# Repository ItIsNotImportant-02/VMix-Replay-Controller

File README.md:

# vMix Replay Controller

Vlastní hardwarový ovladač pro vMix Replay ve stylu EVS: RGB tlačítka, páka pro rychlost, jog kolečko. Vlastní PCB (KiCad, osazení JLCPCB), vlastní firmware, 3D tištěná krabička.

- Plán projektu: [docs/PLAN.md](docs/PLAN.md)
- Dashboard postupu: https://claude.ai/artifact/F6eHfhQ5NSxDFNfWmzDA3g
- Deep Research prompty: [docs/research/](docs/research/)

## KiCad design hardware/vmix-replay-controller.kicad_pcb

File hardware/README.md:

# Hardware (KiCad 9)

Hlavní deska ovladače. Popis návrhu a otevřené body: [DESIGN.md](DESIGN.md), piny a mapování tlačítek/LED: [PINMAP.md](PINMAP.md).

- `vmix-replay-controller.kicad_pro` a `vmix-replay-controller.kicad_sch`: projekt a jednostránkové blokové schéma (generované z `tools/circuit.py` + `tools/layout.py`, needitovat ručně)
- `lib/`: vlastní symboly a footprinty (PB26, TS5, IS31FL3236A QFN-44)
- `tools/`: generátor schématu a footprintů (`gen.py`), kontrola netlistu (`verify.py`), rozmístění desky ze schématu (`pcb.py`) a export BOM + CPL pro JLCPCB (`jlc.py`)
- `production/`: výrobní data pro JLCPCB (Gerber, BOM, CPL), doplní se po návrhu desky

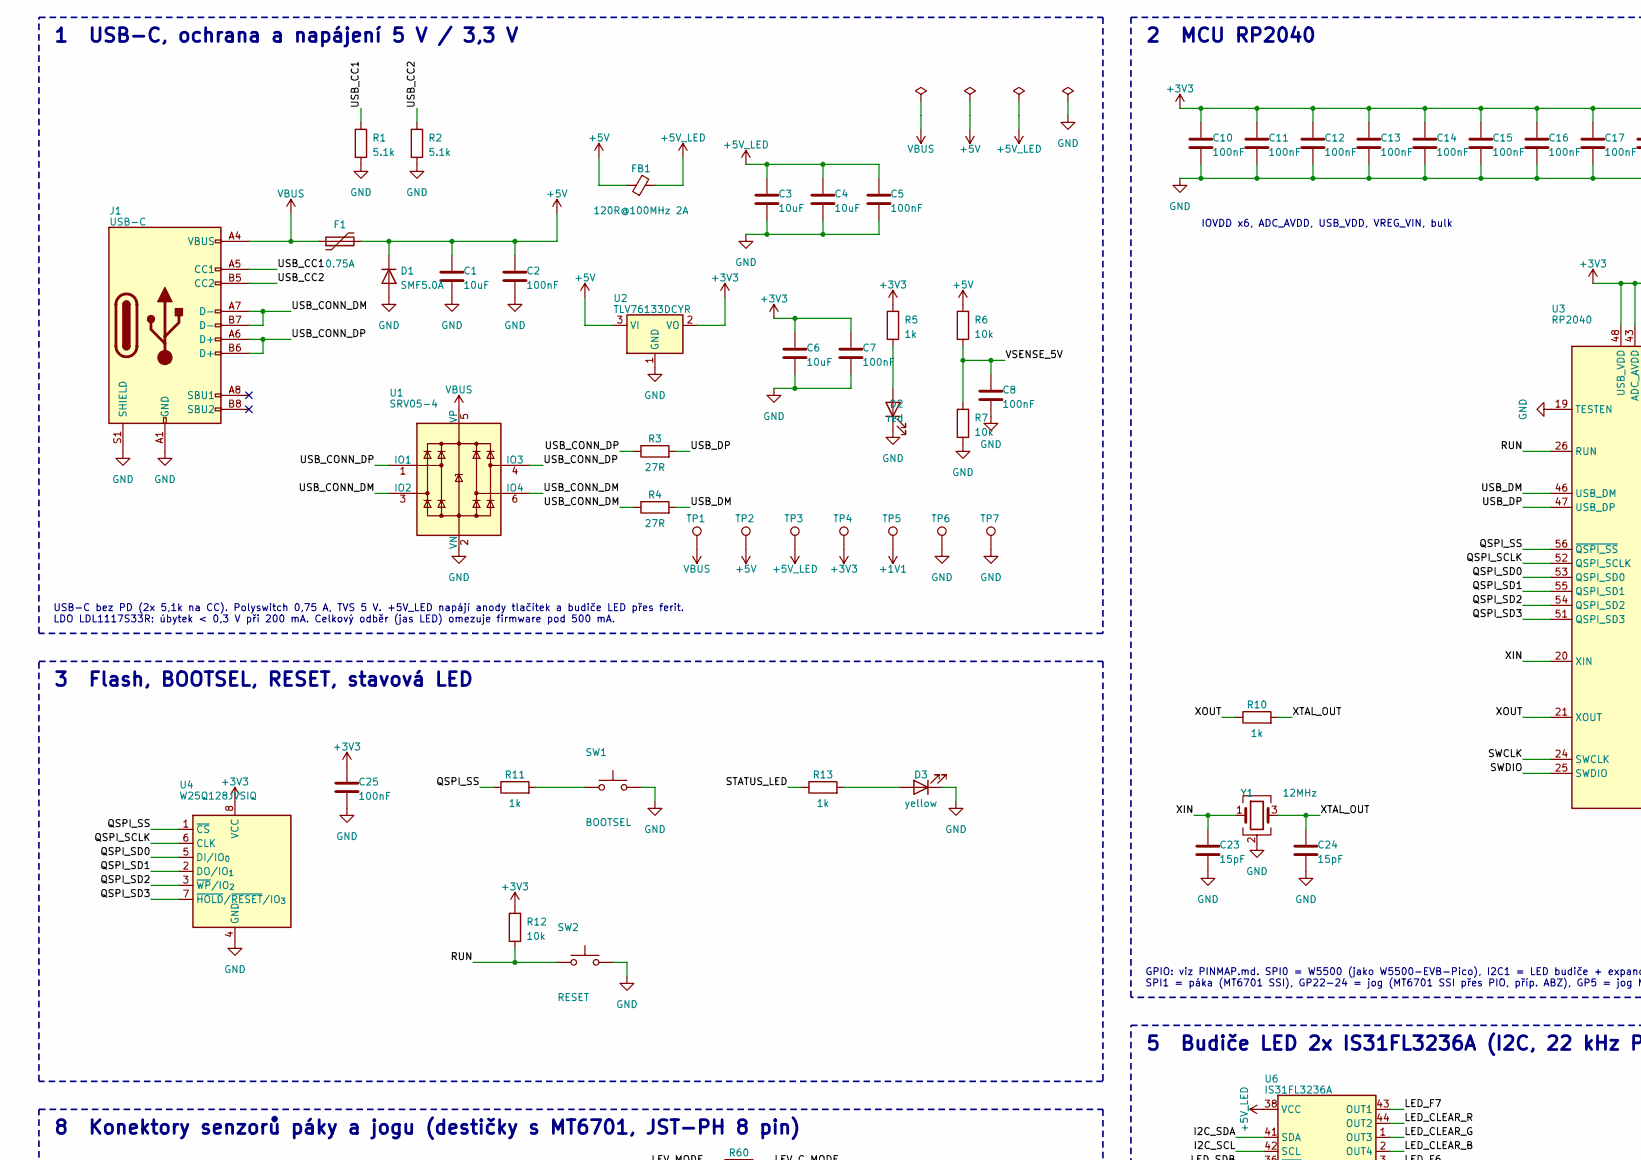
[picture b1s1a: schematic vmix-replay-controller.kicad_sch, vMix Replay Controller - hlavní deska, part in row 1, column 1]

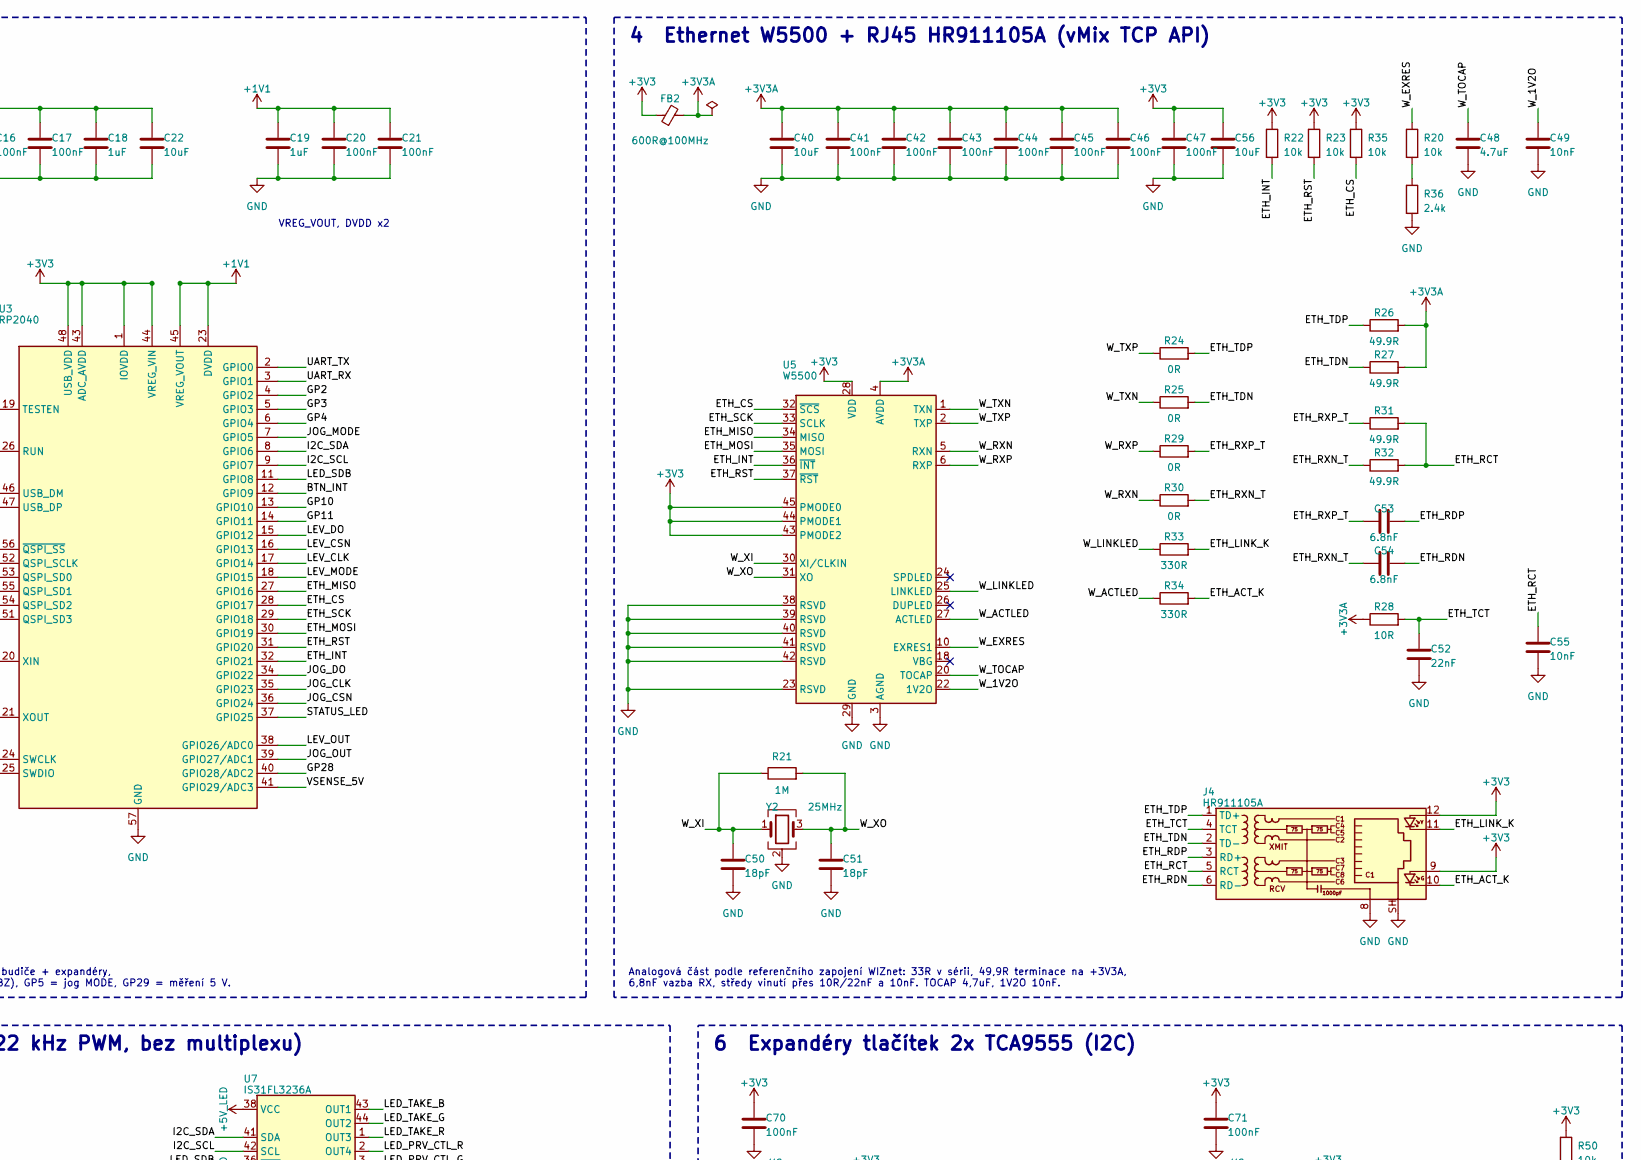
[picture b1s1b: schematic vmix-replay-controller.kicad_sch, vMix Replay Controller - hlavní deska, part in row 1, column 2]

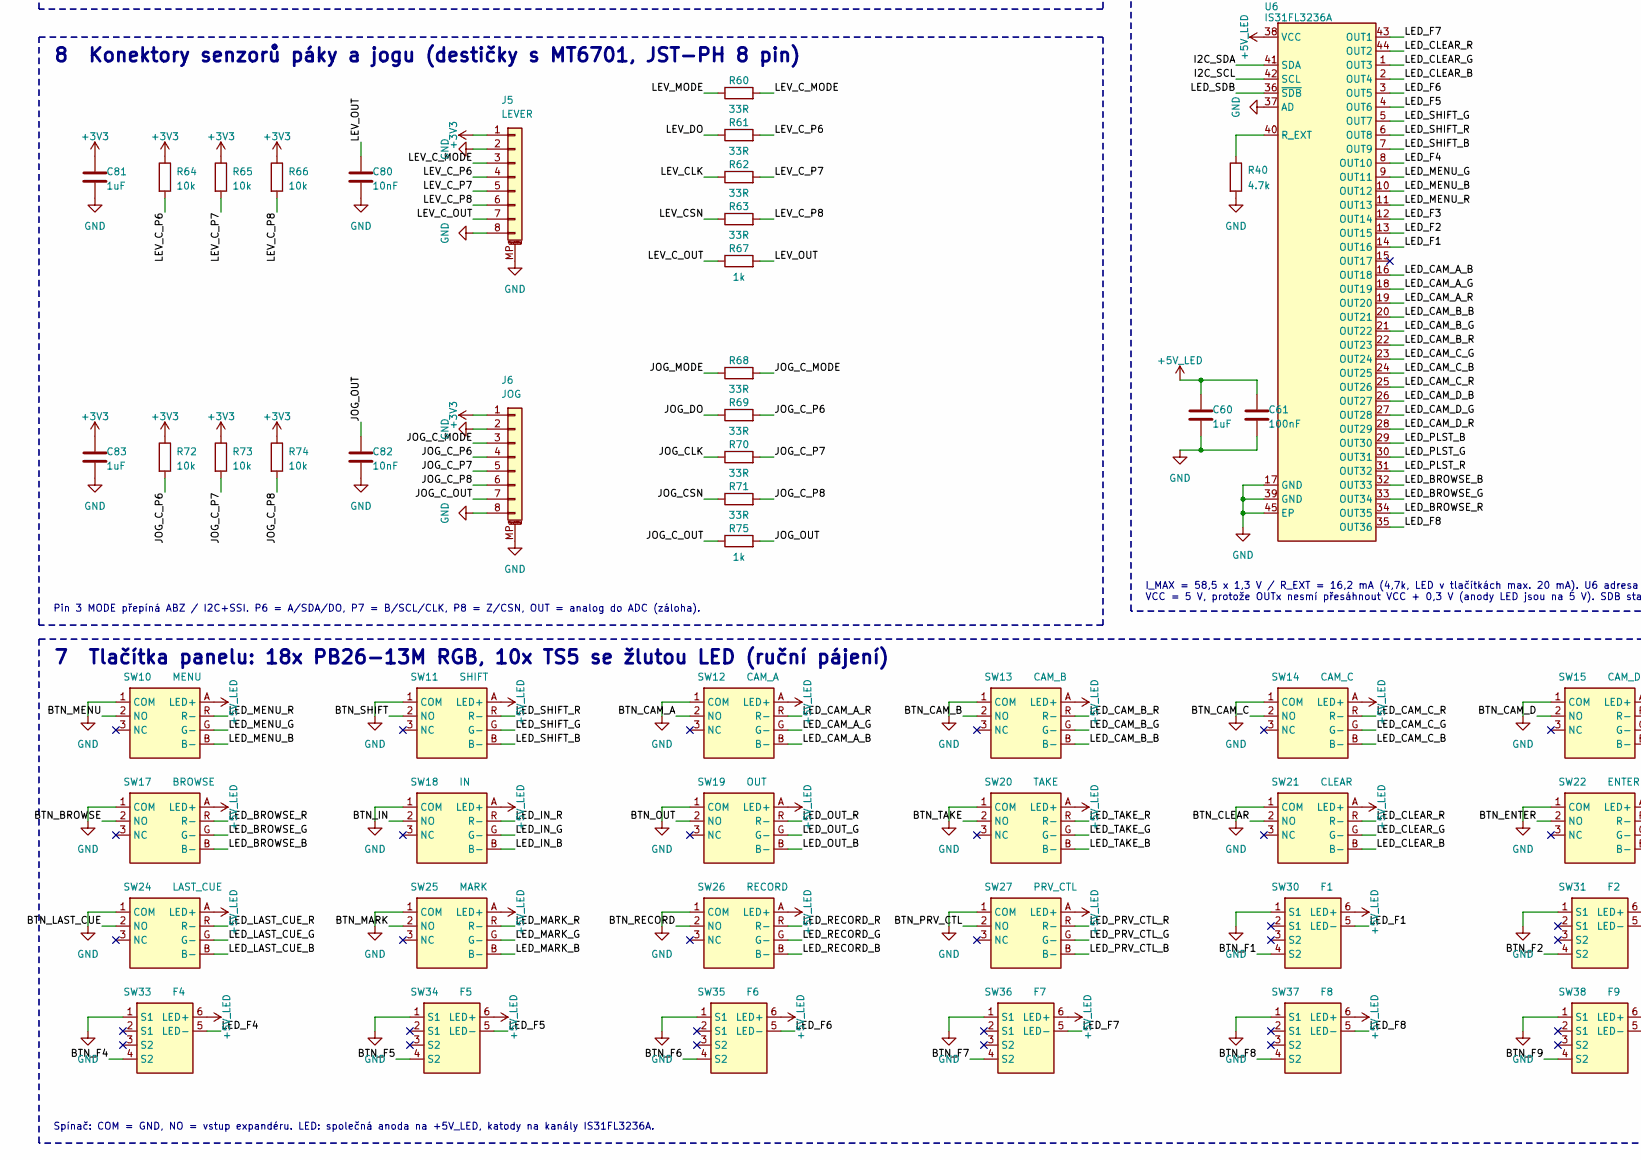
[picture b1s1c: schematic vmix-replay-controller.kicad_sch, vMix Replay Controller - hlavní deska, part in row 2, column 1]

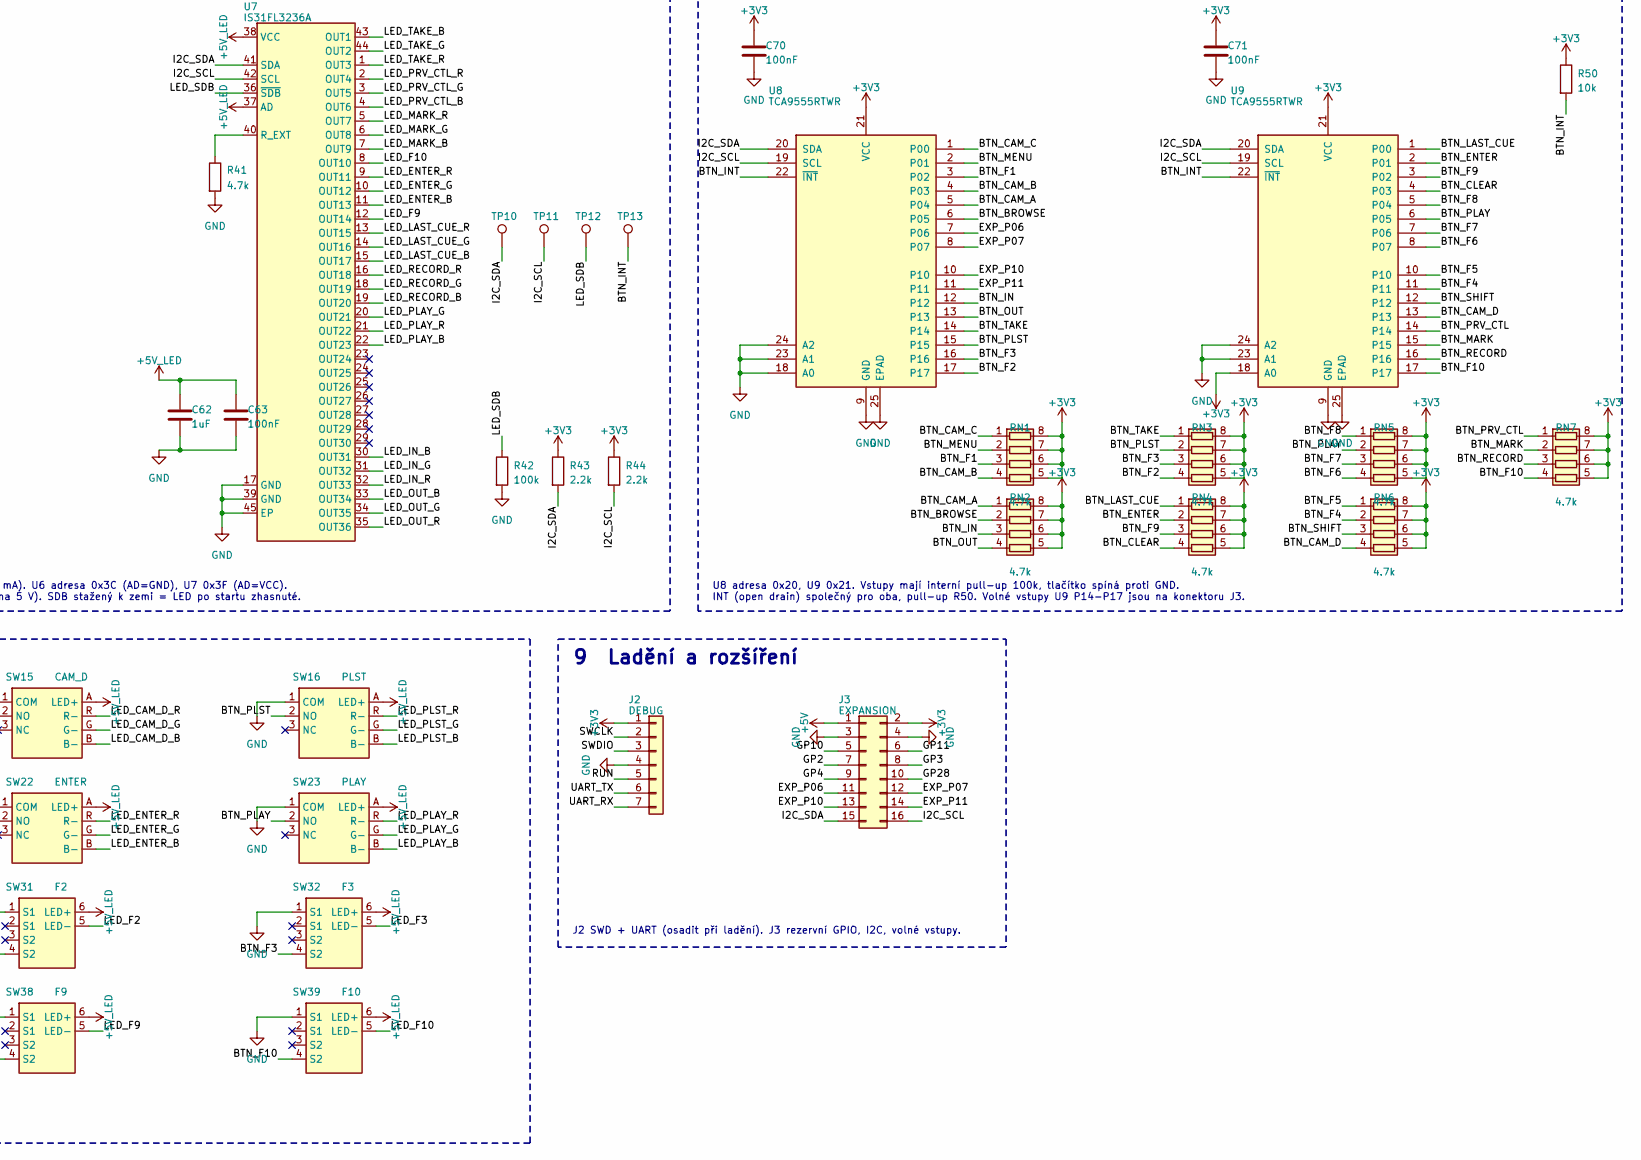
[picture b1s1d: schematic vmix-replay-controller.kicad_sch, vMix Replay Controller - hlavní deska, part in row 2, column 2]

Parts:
C1, C3, C4, C6, C22, C40, C56: 10uF; C_0805_2012Metric; LCSC C15850
C2, C5, C7, C8, C10, C11, C12, C13, C14, C15, C16, C17, C20, C21, C25, C41, C42, C43, C44, C45, C46, C47, C61, C63, C70, C71: 100nF; C_0603_1608Metric; LCSC C14663
C18, C19, C60, C62, C81, C83: 1uF; C_0603_1608Metric; LCSC C15849
C23, C24: 15pF; C_0603_1608Metric; LCSC C1644
C48: 4.7uF; C_0603_1608Metric; LCSC C19666
C49, C55, C80, C82: 10nF; C_0603_1608Metric; LCSC C57112
C50, C51: 18pF; C_0603_1608Metric; LCSC C1647
C52: 22nF; C_0603_1608Metric; LCSC C21122
C53, C54: 6.8nF; C_0603_1608Metric; LCSC C1631
D1: SMF5.0A; D_SOD-123F; MPN hongjiacheng SMF5.0A; LCSC C19077497
D2: red; LED_0603_1608Metric; MPN KENTO KT-0603R; LCSC C2286
D3: yellow; LED_0603_1608Metric; MPN NationStar NCD0603Y2; LCSC C89811
F1: 0.75A; Fuse_1206_3216Metric; MPN JK-nSMD075/6V; LCSC C2830242
FB1: 120R@100MHz 2A; L_0603_1608Metric; MPN BLM18PG121SN1D; LCSC C14709
FB2: 600R@100MHz; L_0805_2012Metric; LCSC C1017
J1: USB-C; USB_C_Receptacle_HRO_TYPE-C-31-M-12; MPN TYPE-C-31-M-12; LCSC C165948
J2: DEBUG; PinHeader_1x07_P2.54mm_Vertical
J3: EXPANSION; PinHeader_2x08_P2.54mm_Vertical
J4: HR911105A; RJ45_Hanrun_HR911105A_Horizontal; LCSC C12074
J5: LEVER; JST_PH_S8B-PH-SM4-TB_1x08-1MP_P2.00mm_Horizontal; MPN S8B-PH-SM4-TB; LCSC C265121
J6: JOG; JST_PH_S8B-PH-SM4-TB_1x08-1MP_P2.00mm_Horizontal; MPN S8B-PH-SM4-TB; LCSC C265121
R1, R2: 5.1k; R_0603_1608Metric; Tolerance 1%; LCSC C23186
R3, R4: 27R; R_0603_1608Metric; Tolerance 1%; LCSC C25190
R5, R10, R11, R13, R67, R75: 1k; R_0603_1608Metric; Tolerance 1%; LCSC C21190
R6, R7, R12, R20, R22, R23, R35, R50, R64, R65, R66, R72, R73, R74: 10k; R_0603_1608Metric; Tolerance 1%; LCSC C25804
R21: 1M; R_0603_1608Metric; Tolerance 1%; LCSC C22935
R24, R25, R29, R30: 0R; R_0603_1608Metric; Tolerance 1%; LCSC C21189
R26, R27, R31, R32: 49.9R; R_0603_1608Metric; Tolerance 1%; LCSC C23185
R28: 10R; R_0603_1608Metric; Tolerance 1%; LCSC C22859
R33, R34: 330R; R_0603_1608Metric; Tolerance 1%; LCSC C23138
R36: 2.4k; R_0603_1608Metric; Tolerance 1%; LCSC C22940
R40, R41: 4.7k; R_0603_1608Metric; Tolerance 1%; LCSC C23162
R42: 100k; R_0603_1608Metric; Tolerance 1%; LCSC C25803
R43, R44: 2.2k; R_0603_1608Metric; Tolerance 1%; LCSC C4190
R60, R61, R62, R63, R68, R69, R70, R71: 33R; R_0603_1608Metric; Tolerance 1%; LCSC C23140
RN1, RN2, RN3, RN4, RN5, RN6, RN7: 4.7k; R_Array_Convex_4x0603; MPN 4D03WGJ0472T5E; LCSC C1980
SW1: BOOTSEL; SW_Push_1P1T_XKB_TS-1187A; LCSC C318884
SW2: RESET; SW_Push_1P1T_XKB_TS-1187A; LCSC C318884
SW10: MENU; PB26-13M-RGB; MPN PB26-13M-B-WT-RGB-N
SW11: SHIFT; PB26-13M-RGB; MPN PB26-13M-B-WT-RGB-N
SW12: CAM_A; PB26-13M-RGB; MPN PB26-13M-B-WT-RGB-N
SW13: CAM_B; PB26-13M-RGB; MPN PB26-13M-B-WT-RGB-N
SW14: CAM_C; PB26-13M-RGB; MPN PB26-13M-B-WT-RGB-N
SW15: CAM_D; PB26-13M-RGB; MPN PB26-13M-B-WT-RGB-N
SW16: PLST; PB26-13M-RGB; MPN PB26-13M-B-WT-RGB-N
SW17: BROWSE; PB26-13M-RGB; MPN PB26-13M-B-WT-RGB-N
SW18: IN; PB26-13M-RGB; MPN PB26-13M-B-WT-RGB-N
SW19: OUT; PB26-13M-RGB; MPN PB26-13M-B-WT-RGB-N
SW20: TAKE; PB26-13M-RGB; MPN PB26-13M-B-WT-RGB-N
SW21: CLEAR; PB26-13M-RGB; MPN PB26-13M-B-WT-RGB-N
SW22: ENTER; PB26-13M-RGB; MPN PB26-13M-B-WT-RGB-N
SW23: PLAY; PB26-13M-RGB; MPN PB26-13M-B-WT-RGB-N
SW24: LAST_CUE; PB26-13M-RGB; MPN PB26-13M-B-WT-RGB-N
SW25: MARK; PB26-13M-RGB; MPN PB26-13M-B-WT-RGB-N
SW26: RECORD; PB26-13M-RGB; MPN PB26-13M-B-WT-RGB-N
SW27: PRV_CTL; PB26-13M-RGB; MPN PB26-13M-B-WT-RGB-N
SW30: F1; TS5-9.2mm-LED; MPN TS5 yellow
SW31: F2; TS5-9.2mm-LED; MPN TS5 yellow
SW32: F3; TS5-9.2mm-LED; MPN TS5 yellow
SW33: F4; TS5-9.2mm-LED; MPN TS5 yellow
SW34: F5; TS5-9.2mm-LED; MPN TS5 yellow
SW35: F6; TS5-9.2mm-LED; MPN TS5 yellow
SW36: F7; TS5-9.2mm-LED; MPN TS5 yellow
SW37: F8; TS5-9.2mm-LED; MPN TS5 yellow
SW38: F9; TS5-9.2mm-LED; MPN TS5 yellow
SW39: F10; TS5-9.2mm-LED; MPN TS5 yellow
TP1: VBUS; TestPoint_Pad_D1.5mm
TP2: +5V; TestPoint_Pad_D1.5mm
TP3: +5V_LED; TestPoint_Pad_D1.5mm
TP4: +3V3; TestPoint_Pad_D1.5mm
TP5: +1V1; TestPoint_Pad_D1.5mm
TP6, TP7: GND; TestPoint_Pad_D1.5mm
TP10: I2C_SDA; TestPoint_Pad_D1.5mm
TP11: I2C_SCL; TestPoint_Pad_D1.5mm
TP12: LED_SDB; TestPoint_Pad_D1.5mm
TP13: BTN_INT; TestPoint_Pad_D1.5mm
U1: SRV05-4; SOT-23-6; MPN hongjiacheng SRV05-4; LCSC C7420376
U2: TLV76133DCYR; SOT-223-3_TabPin2; MPN TLV76133DCYR; LCSC C7527500
U3: RP2040; QFN-56-1EP_7x7mm_P0.4mm_EP3.2x3.2mm; LCSC C2040
U4: W25Q128JVSIQ; SOIC-8_5.3x5.3mm_P1.27mm; LCSC C97521
U5: W5500; LQFP-48_7x7mm_P0.5mm; LCSC C32843
U6, U7: IS31FL3236A; QFN-44-1EP_5x5mm_P0.4mm; MPN IS31FL3236A-QFLS2-TR; LCSC C246443
U8, U9: TCA9555RTWR; Texas_RTW_WQFN-24-1EP_4x4mm_P0.5mm_EP2.7x2.7mm; LCSC C140277
Y1: 12MHz; Crystal_SMD_3225-4Pin_3.2x2.5mm; MPN TX322512M4DBDE2T; LCSC C5310728
Y2: 25MHz; Crystal_SMD_3225-4Pin_3.2x2.5mm; MPN X322525MOB4SI (CL 12 pF); LCSC C9006

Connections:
+1V1: C19.1, C20.1, C21.1, TP5.1, U3.23 (DVDD), U3.45 (VREG_VOUT), U3.50 (DVDD)
+3V3: C6.1, C7.1, C10.1, C11.1, C12.1, C13.1, C14.1, C15.1, C16.1, C17.1, C18.1, C22.1, C25.1, C47.1, C56.1, C70.1, C71.1, C81.1, C83.1, FB2.1, J2.1, J3.2, J4.9, J4.12, J5.1, J6.1, R5.1, R12.1, R22.1, R23.1, R35.1, R43.1, R44.1, R50.1, R64.1, R65.1, R66.1, R72.1, R73.1, R74.1, RN1.5 (R4.2), RN1.6 (R3.2), RN1.7 (R2.2), RN1.8 (R1.2), RN2.5 (R4.2), RN2.6 (R3.2), RN2.7 (R2.2), RN2.8 (R1.2), RN3.5 (R4.2), RN3.6 (R3.2), RN3.7 (R2.2), RN3.8 (R1.2), RN4.5 (R4.2), RN4.6 (R3.2), RN4.7 (R2.2), RN4.8 (R1.2), RN5.5 (R4.2), RN5.6 (R3.2), RN5.7 (R2.2), RN5.8 (R1.2), RN6.5 (R4.2), RN6.6 (R3.2), RN6.7 (R2.2), RN6.8 (R1.2), RN7.5 (R4.2), RN7.6 (R3.2), RN7.7 (R2.2), RN7.8 (R1.2), TP4.1, U2.2 (VO), U3.1 (IOVDD), U3.10 (IOVDD), U3.22 (IOVDD), U3.33 (IOVDD), U3.42 (IOVDD), U3.43 (ADC_AVDD), U3.44 (VREG_VIN), U3.48 (USB_VDD), U3.49 (IOVDD), U4.8 (VCC), U5.28 (VDD), U5.43 (PMODE2), U5.44 (PMODE1), U5.45 (PMODE0), U8.21 (VCC), U9.18 (A0), U9.21 (VCC)
+3V3A: C40.1, C41.1, C42.1, C43.1, C44.1, C45.1, C46.1, FB2.2, R26.2, R27.2, R28.1, U5.4 (AVDD), U5.8 (AVDD), U5.11 (AVDD), U5.15 (AVDD), U5.17 (AVDD), U5.21 (AVDD)
+5V: C1.1, C2.1, D1.1 (K), F1.2, FB1.1, J3.1, R6.1, TP2.1, U2.3 (VI)
+5V_LED: C3.1, C4.1, C5.1, C60.1, C61.1, C62.1, C63.1, FB1.2, SW10.A (LED+), SW11.A (LED+), SW12.A (LED+), SW13.A (LED+), SW14.A (LED+), SW15.A (LED+), SW16.A (LED+), SW17.A (LED+), SW18.A (LED+), SW19.A (LED+), SW20.A (LED+), SW21.A (LED+), SW22.A (LED+), SW23.A (LED+), SW24.A (LED+), SW25.A (LED+), SW26.A (LED+), SW27.A (LED+), SW30.6 (LED+), SW31.6 (LED+), SW32.6 (LED+), SW33.6 (LED+), SW34.6 (LED+), SW35.6 (LED+), SW36.6 (LED+), SW37.6 (LED+), SW38.6 (LED+), SW39.6 (LED+), TP3.1, U6.38 (VCC), U7.37 (AD), U7.38 (VCC)
/BTN_BROWSE: RN2.2 (R2.1), SW17.2 (NO), U8.6 (P05)
/BTN_CAM_A: RN2.1 (R1.1), SW12.2 (NO), U8.5 (P04)
/BTN_CAM_B: RN1.4 (R4.1), SW13.2 (NO), U8.4 (P03)
/BTN_CAM_C: RN1.1 (R1.1), SW14.2 (NO), U8.1 (P00)
/BTN_CAM_D: RN6.4 (R4.1), SW15.2 (NO), U9.13
/BTN_CLEAR: RN4.4 (R4.1), SW21.2 (NO), U9.4 (P03)
/BTN_ENTER: RN4.2 (R2.1), SW22.2 (NO), U9.2 (P01)
/BTN_F1: RN1.3 (R3.1), SW30.4 (S2), U8.3 (P02)
/BTN_F2: RN3.4 (R4.1), SW31.4 (S2), U8.17
/BTN_F3: RN3.3 (R3.1), SW32.4 (S2), U8.16
/BTN_F4: RN6.2 (R2.1), SW33.4 (S2), U9.11
/BTN_F5: RN6.1 (R1.1), SW34.4 (S2), U9.10
/BTN_F6: RN5.4 (R4.1), SW35.4 (S2), U9.8 (P07)
/BTN_F7: RN5.3 (R3.1), SW36.4 (S2), U9.7 (P06)
/BTN_F8: RN5.1 (R1.1), SW37.4 (S2), U9.5 (P04)
/BTN_F9: RN4.3 (R3.1), SW38.4 (S2), U9.3 (P02)
/BTN_F10: RN7.4 (R4.1), SW39.4 (S2), U9.17
/BTN_IN: RN2.3 (R3.1), SW18.2 (NO), U8.12
/BTN_INT: R50.2, TP13.1, U3.12 (GPIO9), U8.22 (~INT), U9.22 (~INT)
/BTN_LAST_CUE: RN4.1 (R1.1), SW24.2 (NO), U9.1 (P00)
/BTN_MARK: RN7.2 (R2.1), SW25.2 (NO), U9.15
/BTN_MENU: RN1.2 (R2.1), SW10.2 (NO), U8.2 (P01)
/BTN_OUT: RN2.4 (R4.1), SW19.2 (NO), U8.13
/BTN_PLAY: RN5.2 (R2.1), SW23.2 (NO), U9.6 (P05)
/BTN_PLST: RN3.2 (R2.1), SW16.2 (NO), U8.15
/BTN_PRV_CTL: RN7.1 (R1.1), SW27.2 (NO), U9.14
/BTN_RECORD: RN7.3 (R3.1), SW26.2 (NO), U9.16
/BTN_SHIFT: RN6.3 (R3.1), SW11.2 (NO), U9.12
/BTN_TAKE: RN3.1 (R1.1), SW20.2 (NO), U8.14
/ETH_ACT_K: J4.10, R34.2
/ETH_CS: R35.2, U3.28 (GPIO17), U5.32 (~SCS)
/ETH_INT: R22.2, U3.32 (GPIO21), U5.36 (~INT)
/ETH_LINK_K: J4.11, R33.2
/ETH_MISO: U3.27 (GPIO16), U5.34 (MISO)
/ETH_MOSI: U3.30 (GPIO19), U5.35 (MOSI)
/ETH_RCT: C55.1, J4.5 (RCT), R31.2, R32.2
/ETH_RDN: C54.2, J4.6 (RD-)
/ETH_RDP: C53.2, J4.3 (RD+)
/ETH_RST: R23.2, U3.31 (GPIO20), U5.37 (~RST)
/ETH_RXN_T: C54.1, R30.2, R32.1
/ETH_RXP_T: C53.1, R29.2, R31.1
/ETH_SCK: U3.29 (GPIO18), U5.33 (SCLK)
/ETH_TCT: C52.1, J4.4 (TCT), R28.2
/ETH_TDN: J4.2 (TD-), R25.2, R27.1
/ETH_TDP: J4.1 (TD+), R24.2, R26.1
/EXP_P06: J3.11, U8.7 (P06)
/EXP_P07: J3.12, U8.8 (P07)
/EXP_P10: J3.13, U8.10
/EXP_P11: J3.14, U8.11
/GP2: J3.7, U3.4 (GPIO2)
/GP3: J3.8, U3.5 (GPIO3)
/GP4: J3.9, U3.6 (GPIO4)
/GP10: J3.5, U3.13 (GPIO10)
/GP11: J3.6, U3.14 (GPIO11)
/GP28: J3.10, U3.40 (GPIO28/ADC2)
/I2C_SCL: J3.16, R44.2, TP11.1, U3.9 (GPIO7), U6.42 (SCL), U7.42 (SCL), U8.19 (SCL), U9.19 (SCL)
/I2C_SDA: J3.15, R43.2, TP10.1, U3.8 (GPIO6), U6.41 (SDA), U7.41 (SDA), U8.20 (SDA), U9.20 (SDA)
/JOG_CLK: R70.1, U3.35 (GPIO23)
/JOG_CSN: R71.1, U3.36 (GPIO24)
/JOG_C_MODE: J6.3, R68.2
/JOG_C_OUT: J6.7, R75.1
/JOG_C_P6: J6.4, R69.2, R72.2
/JOG_C_P7: J6.5, R70.2, R73.2
/JOG_C_P8: J6.6, R71.2, R74.2
/JOG_DO: R69.1, U3.34 (GPIO22)
/JOG_MODE: R68.1, U3.7 (GPIO5)
/JOG_OUT: C82.1, R75.2, U3.39 (GPIO27/ADC1)
/LED_BROWSE_B: SW17.B (B-), U6.32 (OUT33)
/LED_BROWSE_G: SW17.G (G-), U6.33 (OUT34)
/LED_BROWSE_R: SW17.R (R-), U6.34 (OUT35)
/LED_CAM_A_B: SW12.B (B-), U6.16 (OUT18)
/LED_CAM_A_G: SW12.G (G-), U6.18 (OUT19)
/LED_CAM_A_R: SW12.R (R-), U6.19 (OUT20)
/LED_CAM_B_B: SW13.B (B-), U6.20 (OUT21)
/LED_CAM_B_G: SW13.G (G-), U6.21 (OUT22)
/LED_CAM_B_R: SW13.R (R-), U6.22 (OUT23)
/LED_CAM_C_B: SW14.B (B-), U6.24 (OUT25)
/LED_CAM_C_G: SW14.G (G-), U6.23 (OUT24)
/LED_CAM_C_R: SW14.R (R-), U6.25 (OUT26)
/LED_CAM_D_B: SW15.B (B-), U6.26 (OUT27)
/LED_CAM_D_G: SW15.G (G-), U6.27 (OUT28)
/LED_CAM_D_R: SW15.R (R-), U6.28 (OUT29)
/LED_CLEAR_B: SW21.B (B-), U6.2 (OUT4)
/LED_CLEAR_G: SW21.G (G-), U6.1 (OUT3)
/LED_CLEAR_R: SW21.R (R-), U6.44 (OUT2)
/LED_ENTER_B: SW22.B (B-), U7.11 (OUT13)
/LED_ENTER_G: SW22.G (G-), U7.10 (OUT12)
/LED_ENTER_R: SW22.R (R-), U7.9 (OUT11)
/LED_F1: SW30.5 (LED-), U6.14 (OUT16)
/LED_F2: SW31.5 (LED-), U6.13 (OUT15)
/LED_F3: SW32.5 (LED-), U6.12 (OUT14)
/LED_F4: SW33.5 (LED-), U6.8 (OUT10)
/LED_F5: SW34.5 (LED-), U6.4 (OUT6)
/LED_F6: SW35.5 (LED-), U6.3 (OUT5)
/LED_F7: SW36.5 (LED-), U6.43 (OUT1)
/LED_F8: SW37.5 (LED-), U6.35 (OUT36)
/LED_F9: SW38.5 (LED-), U7.12 (OUT14)
/LED_F10: SW39.5 (LED-), U7.8 (OUT10)
/LED_IN_B: SW18.B (B-), U7.30 (OUT31)
/LED_IN_G: SW18.G (G-), U7.31 (OUT32)
/LED_IN_R: SW18.R (R-), U7.32 (OUT33)
/LED_LAST_CUE_B: SW24.B (B-), U7.15 (OUT17)
/LED_LAST_CUE_G: SW24.G (G-), U7.14 (OUT16)
/LED_LAST_CUE_R: SW24.R (R-), U7.13 (OUT15)
/LED_MARK_B: SW25.B (B-), U7.7 (OUT9)
/LED_MARK_G: SW25.G (G-), U7.6 (OUT8)
/LED_MARK_R: SW25.R (R-), U7.5 (OUT7)
/LED_MENU_B: SW10.B (B-), U6.10 (OUT12)
/LED_MENU_G: SW10.G (G-), U6.9 (OUT11)
/LED_MENU_R: SW10.R (R-), U6.11 (OUT13)
/LED_OUT_B: SW19.B (B-), U7.33 (OUT34)
/LED_OUT_G: SW19.G (G-), U7.34 (OUT35)
/LED_OUT_R: SW19.R (R-), U7.35 (OUT36)
/LED_PLAY_B: SW23.B (B-), U7.22 (OUT23)
/LED_PLAY_G: SW23.G (G-), U7.20 (OUT21)
/LED_PLAY_R: SW23.R (R-), U7.21 (OUT22)
/LED_PLST_B: SW16.B (B-), U6.29 (OUT30)
/LED_PLST_G: SW16.G (G-), U6.30 (OUT31)
/LED_PLST_R: SW16.R (R-), U6.31 (OUT32)
/LED_PRV_CTL_B: SW27.B (B-), U7.4 (OUT6)
/LED_PRV_CTL_G: SW27.G (G-), U7.3 (OUT5)
/LED_PRV_CTL_R: SW27.R (R-), U7.2 (OUT4)
/LED_RECORD_B: SW26.B (B-), U7.19 (OUT20)
/LED_RECORD_G: SW26.G (G-), U7.18 (OUT19)
/LED_RECORD_R: SW26.R (R-), U7.16 (OUT18)
/LED_SDB: R42.1, TP12.1, U3.11 (GPIO8), U6.36 (~SDB), U7.36 (~SDB)
/LED_SHIFT_B: SW11.B (B-), U6.7 (OUT9)
/LED_SHIFT_G: SW11.G (G-), U6.5 (OUT7)
/LED_SHIFT_R: SW11.R (R-), U6.6 (OUT8)
/LED_TAKE_B: SW20.B (B-), U7.43 (OUT1)
/LED_TAKE_G: SW20.G (G-), U7.44 (OUT2)
/LED_TAKE_R: SW20.R (R-), U7.1 (OUT3)
/LEV_CLK: R62.1, U3.17 (GPIO14)
/LEV_CSN: R63.1, U3.16 (GPIO13)
/LEV_C_MODE: J5.3, R60.2
/LEV_C_OUT: J5.7, R67.1
/LEV_C_P6: J5.4, R61.2, R64.2
/LEV_C_P7: J5.5, R62.2, R65.2
/LEV_C_P8: J5.6, R63.2, R66.2
/LEV_DO: R61.1, U3.15 (GPIO12)
/LEV_MODE: R60.1, U3.18 (GPIO15)
/LEV_OUT: C80.1, R67.2, U3.38 (GPIO26/ADC0)
/QSPI_SCLK: U3.52 (QSPI_SCLK), U4.6 (CLK)
/QSPI_SD0: U3.53 (QSPI_SD0), U4.5 (DI/IO_{0})
/QSPI_SD1: U3.55 (QSPI_SD1), U4.2 (DO/IO_{1})
/QSPI_SD2: U3.54 (QSPI_SD2), U4.3 (~WP/IO_{2})
/QSPI_SD3: U3.51 (QSPI_SD3), U4.7 (~HOLD/~RESET/IO_{3})
/QSPI_SS: R11.1, U3.56 (~QSPI_SS), U4.1 (~CS)
/RUN: J2.5, R12.2, SW2.1, U3.26 (RUN)
/STATUS_LED: R13.1, U3.37 (GPIO25)
/SWCLK: J2.2, U3.24 (SWCLK)
/SWDIO: J2.3, U3.25 (SWDIO)
/UART_RX: J2.7, U3.3 (GPIO1)
/UART_TX: J2.6, U3.2 (GPIO0)
/USB_CC1: J1.A5 (CC1), R1.1
/USB_CC2: J1.B5 (CC2), R2.1
/USB_CONN_DM: J1.A7 (D-), J1.B7 (D-), R4.1, U1.3 (IO2), U1.6 (IO4)
/USB_CONN_DP: J1.A6 (D+), J1.B6 (D+), R3.1, U1.1 (IO1), U1.4 (IO3)
/USB_DM: R4.2, U3.46 (USB_DM)
/USB_DP: R3.2, U3.47 (USB_DP)
/VSENSE_5V: C8.1, R6.2, R7.1, U3.41 (GPIO29/ADC3)
/W_1V2O: C49.1, U5.22 (1V2O)
/W_ACTLED: R34.1, U5.27 (ACTLED)
/W_EXRES: R20.1, U5.10 (EXRES1)
/W_LINKLED: R33.1, U5.25 (LINKLED)
/W_RXN: R30.1, U5.5 (RXN)
/W_RXP: R29.1, U5.6 (RXP)
/W_TOCAP: C48.1, U5.20 (TOCAP)
/W_TXN: R25.1, U5.1 (TXN)
/W_TXP: R24.1, U5.2 (TXP)
/W_XI: C50.1, R21.1, U5.30 (XI/CLKIN), Y2.1
/W_XO: C51.1, R21.2, U5.31 (XO), Y2.3
/XIN: C23.1, U3.20 (XIN), Y1.1
/XOUT: R10.1, U3.21 (XOUT)
/XTAL_OUT: C24.1, R10.2, Y1.3
GND: C1.2, C2.2, C3.2, C4.2, C5.2, C6.2, C7.2, C8.2, C10.2, C11.2, C12.2, C13.2, C14.2, C15.2, C16.2, C17.2, C18.2, C19.2, C20.2, C21.2, C22.2, C23.2, C24.2, C25.2, C40.2, C41.2, C42.2, C43.2, C44.2, C45.2, C46.2, C47.2, C48.2, C49.2, C50.2, C51.2, C52.2, C55.2, C56.2, C60.2, C61.2, C62.2, C63.2, C70.2, C71.2, C80.2, C81.2, C82.2, C83.2, D1.2 (A), D2.1 (K), D3.1 (K), J1.A1 (GND), J1.A12 (GND), J1.B1 (GND), J1.B12 (GND), J1.S1 (SHIELD), J2.4, J3.3, J3.4, J4.8, J4.SH, J5.2, J5.8, J5.MP (MountPin), J6.2, J6.8, J6.MP (MountPin), R1.2, R2.2, R7.2, R36.2, R40.2, R41.2, R42.2, SW1.2, SW2.2, SW10.1 (COM), SW11.1 (COM), SW12.1 (COM), SW13.1 (COM), SW14.1 (COM), SW15.1 (COM), SW16.1 (COM), SW17.1 (COM), SW18.1 (COM), SW19.1 (COM), SW20.1 (COM), SW21.1 (COM), SW22.1 (COM), SW23.1 (COM), SW24.1 (COM), SW25.1 (COM), SW26.1 (COM), SW27.1 (COM), SW30.1 (S1), SW31.1 (S1), SW32.1 (S1), SW33.1 (S1), SW34.1 (S1), SW35.1 (S1), SW36.1 (S1), SW37.1 (S1), SW38.1 (S1), SW39.1 (S1), TP6.1, TP7.1, U1.2 (VN), U2.1 (GND), U3.19 (TESTEN), U3.57 (GND), U4.4 (GND), U5.3 (AGND), U5.9 (AGND), U5.14 (AGND), U5.16 (AGND), U5.19 (AGND), U5.23 (RSVD), U5.29 (GND), U5.38 (RSVD), U5.39 (RSVD), U5.40 (RSVD), U5.41 (RSVD), U5.42 (RSVD), U5.48 (AGND), U6.17 (GND), U6.37 (AD), U6.39 (GND), U6.45 (EP), U7.17 (GND), U7.39 (GND), U7.45 (EP), U8.9 (GND), U8.18 (A0), U8.23 (A1), U8.24 (A2), U8.25 (EPAD), U9.9 (GND), U9.23 (A1), U9.24 (A2), U9.25 (EPAD), Y1.2 (G), Y1.4 (G), Y2.2 (G), Y2.4 (G); also elsewhere on the board
unnamed: D2.2 (A), R5.2
unnamed: D3.2 (A), R13.2
unnamed: R11.2, SW1.1
unnamed: R20.2, R36.1
unnamed: R40.1, U6.40 (R_EXT)
unnamed: R41.1, U7.40 (R_EXT)
VBUS: F1.1, J1.A4 (VBUS), J1.A9 (VBUS), J1.B4 (VBUS), J1.B9 (VBUS), TP1.1, U1.5 (VP)

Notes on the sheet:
1 USB-C, ochrana a napájení 5 V / 3,3 V
USB-C bez PD (2x 5,1k na CC). Polyswitch 0,75 A, TVS 5 V. +5V_LED napájí anody tlačítek a budiče LED přes ferit. LDO LDL1117S33R: úbytek < 0,3 V při 200 mA. Celkový odběr (jas LED) omezuje firmware pod 500 mA.
2 MCU RP2040
GPIO: viz PINMAP.md. SPI0 = W5500 (jako W5500-EVB-Pico), I2C1 = LED budiče + expandéry, SPI1 = páka (MT6701 SSI), GP22-24 = jog (MT6701 SSI přes PIO, příp. ABZ), GP5 = jog MODE, GP29 = měření 5 V.
IOVDD x6, ADC_AVDD, USB_VDD, VREG_VIN, bulk
VREG_VOUT, DVDD x2
4 Ethernet W5500 + RJ45 HR911105A (vMix TCP API)
Analogová část podle referenčního zapojení WIZnet: 33R v sérii, 49,9R terminace na +3V3A, 6,8nF vazba RX, středy vinutí přes 10R/22nF a 10nF. TOCAP 4,7uF, 1V2O 10nF.
3 Flash, BOOTSEL, RESET, stavová LED
5 Budiče LED 2x IS31FL3236A (I2C, 22 kHz PWM, bez multiplexu)
I_MAX = 58,5 x 1,3 V / R_EXT = 16,2 mA (4,7k, LED v tlačítkách max. 20 mA). U6 adresa 0x3C (AD=GND), U7 0x3F (AD=VCC). VCC = 5 V, protože OUTx nesmí přesáhnout VCC + 0,3 V (anody LED jsou na 5 V). SDB stažený k zemi = LED po startu zhasnuté.
6 Expandéry tlačítek 2x TCA9555 (I2C)
U8 adresa 0x20, U9 0x21. Vstupy mají interní pull-up 100k, tlačítko spíná proti GND. INT (open drain) společný pro oba, pull-up R50. Volné vstupy U9 P14-P17 jsou na konektoru J3.
7 Tlačítka panelu: 18x PB26-13M RGB, 10x TS5 se žlutou LED (ruční pájení)
Spínač: COM = GND, NO = vstup expandéru. LED: společná anoda na +5V_LED, katody na kanály IS31FL3236A.
8 Konektory senzorů páky a jogu (destičky s MT6701, JST-PH 8 pin)
Pin 3 MODE přepíná ABZ / I2C+SSI. P6 = A/SDA/DO, P7 = B/SCL/CLK, P8 = Z/CSN, OUT = analog do ADC (záloha).
9 Ladění a rozšíření
J2 SWD + UART (osadit při ladění). J3 rezervní GPIO, I2C, volné vstupy.

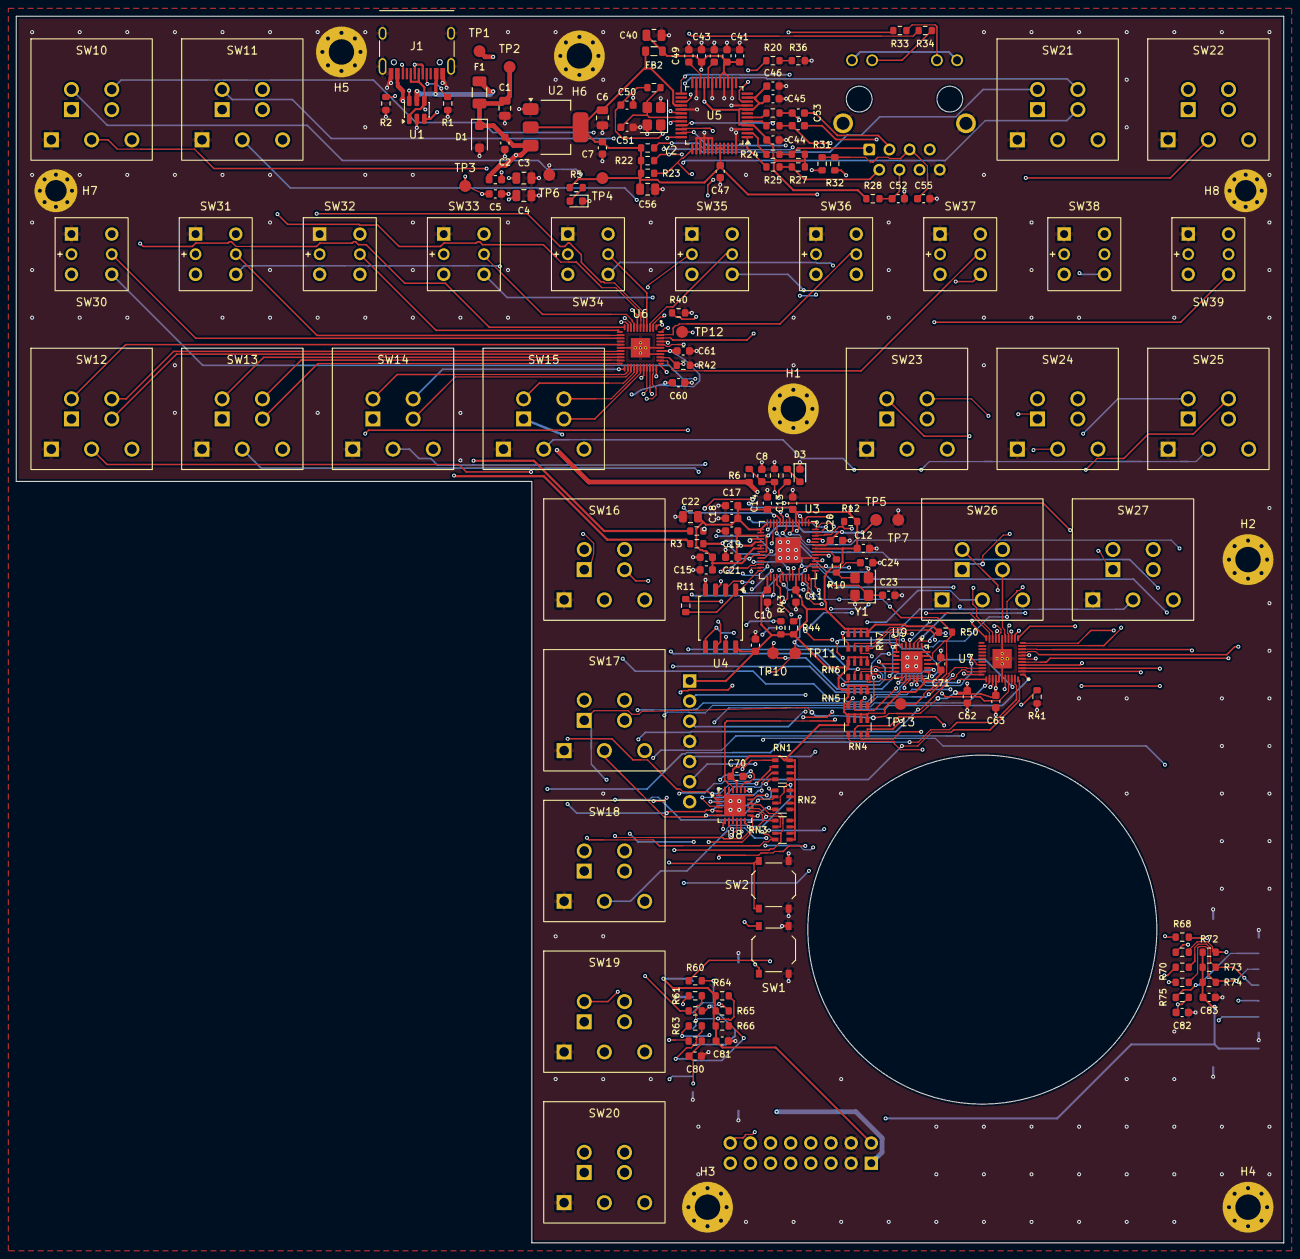
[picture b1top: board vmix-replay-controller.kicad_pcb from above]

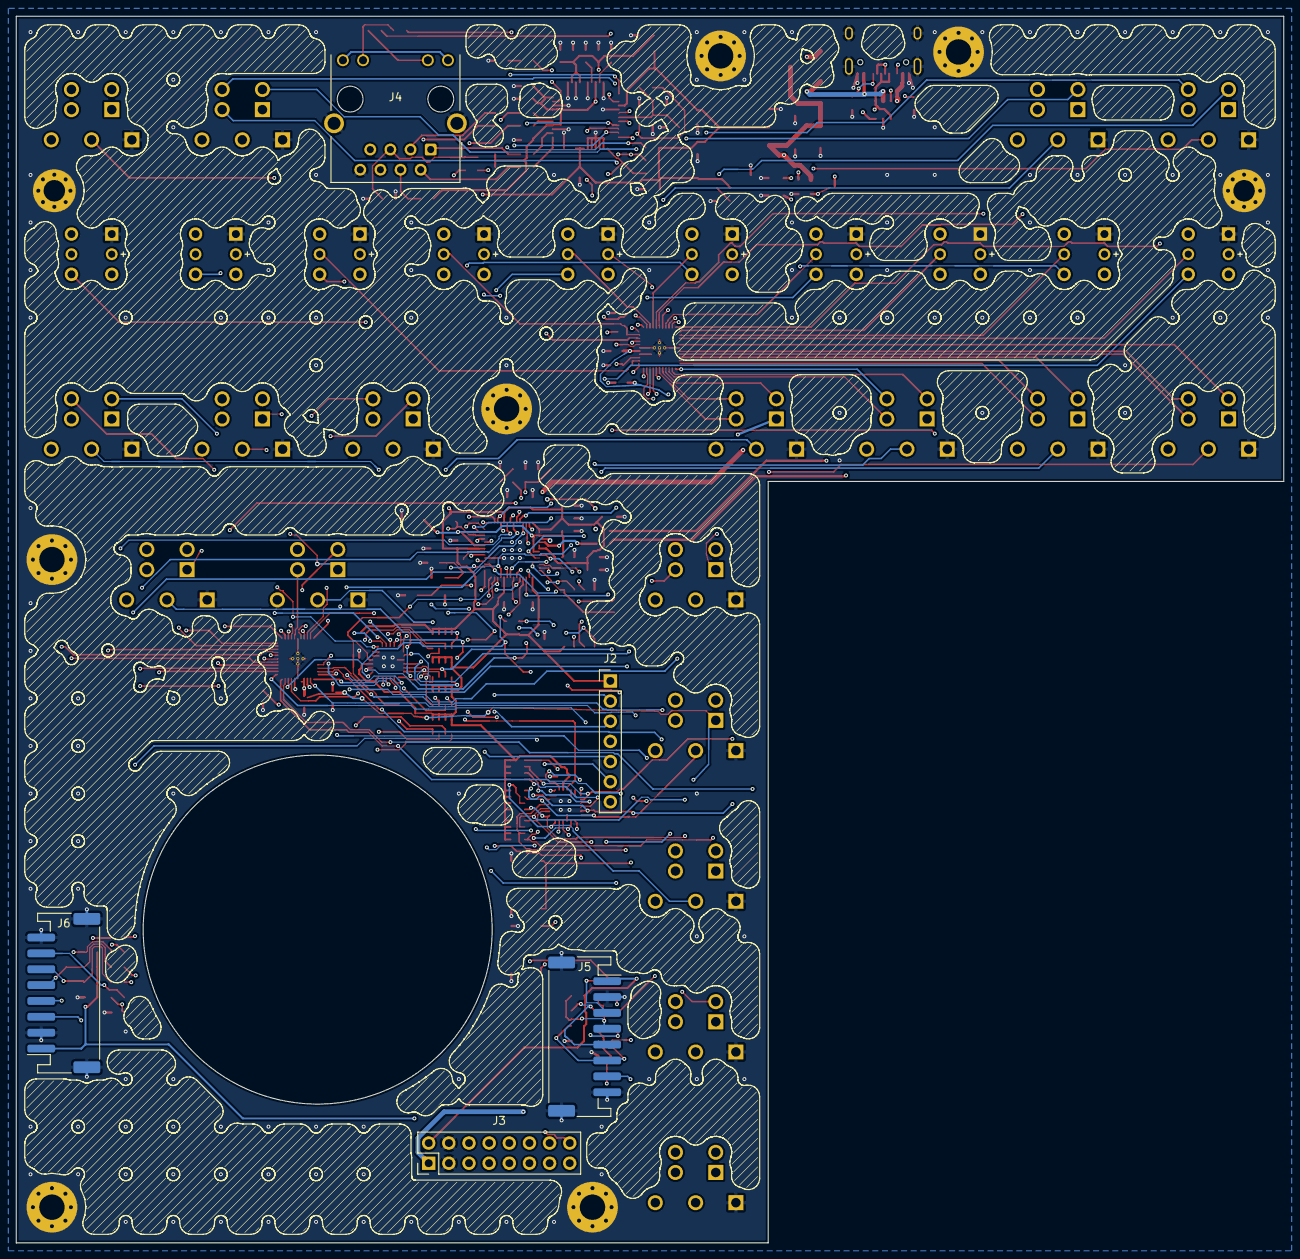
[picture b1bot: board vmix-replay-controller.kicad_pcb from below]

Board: 4 copper layers, 159.8 x 154.7 mm, 180 parts (5 on the bottom side), 188 nets.

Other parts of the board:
H1, H2, H3, H4, H5, H6: M3; MountingHole_3.2mm_M3_Pad_Via
H7, H8: M2.5; MountingHole_2.7mm_M2.5_Pad_Via

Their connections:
GND: H1.1, H2.1, H3.1, H4.1, H5.1, H6.1, H7.1, H8.1; also elsewhere on the board

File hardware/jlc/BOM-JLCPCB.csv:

Comment,Designator,Footprint,LCSC Part #
10uF,"C1,C3,C4,C6,C22,C40,C56",C_0805_2012Metric,C15850
100nF,"C2,C5,C7,C8,C10,C11,C12,C13,C14,C15,C16,C17,C20,C21,C25,C41,C42,C43,C44,C45,C46,C47,C61,C63,C70,C71",C_0603_1608Metric,C14663
1uF,"C18,C19,C60,C62,C81,C83",C_0603_1608Metric,C15849
15pF,"C23,C24",C_0603_1608Metric,C1644
4.7uF,C48,C_0603_1608Metric,C19666
10nF,"C49,C55,C80,C82",C_0603_1608Metric,C57112
18pF,"C50,C51",C_0603_1608Metric,C1647
22nF,C52,C_0603_1608Metric,C21122
6.8nF,"C53,C54",C_0603_1608Metric,C1631
SMF5.0A,D1,D_SOD-123F,C19077497
red,D2,LED_0603_1608Metric,C2286
yellow,D3,LED_0603_1608Metric,C89811
0.75A,F1,Fuse_1206_3216Metric,C2830242
120R@100MHz 2A,FB1,L_0603_1608Metric,C14709
600R@100MHz,FB2,L_0805_2012Metric,C1017
USB-C,J1,USB_C_Receptacle_HRO_TYPE-C-31-M-12,C165948
5.1k,"R1,R2",R_0603_1608Metric,C23186
27R,"R3,R4",R_0603_1608Metric,C25190
1k,"R5,R10,R11,R13,R67,R75",R_0603_1608Metric,C21190
10k,"R6,R7,R12,R20,R22,R23,R35,R50,R64,R65,R66,R72,R73,R74",R_0603_1608Metric,C25804
1M,R21,R_0603_1608Metric,C22935
0R,"R24,R25,R29,R30",R_0603_1608Metric,C21189
49.9R,"R26,R27,R31,R32",R_0603_1608Metric,C23185
10R,R28,R_0603_1608Metric,C22859
330R,"R33,R34",R_0603_1608Metric,C23138
2.4k,R36,R_0603_1608Metric,C22940
4.7k,"R40,R41",R_0603_1608Metric,C23162
100k,R42,R_0603_1608Metric,C25803
2.2k,"R43,R44",R_0603_1608Metric,C4190
33R,"R60,R61,R62,R63,R68,R69,R70,R71",R_0603_1608Metric,C23140
4.7k,"RN1,RN2,RN3,RN4,RN5,RN6,RN7",R_Array_Convex_4x0603,C1980
BOOTSEL,SW1,SW_Push_1P1T_XKB_TS-1187A,C318884
RESET,SW2,SW_Push_1P1T_XKB_TS-1187A,C318884
SRV05-4,U1,SOT-23-6,C7420376
TLV76133DCYR,U2,SOT-223-3_TabPin2,C7527500
RP2040,U3,QFN-56-1EP_7x7mm_P0.4mm_EP3.2x3.2mm,C2040
W25Q128JVSIQ,U4,SOIC-8_5.3x5.3mm_P1.27mm,C97521
W5500,U5,LQFP-48_7x7mm_P0.5mm,C32843
IS31FL3236A,"U6,U7",QFN-44-1EP_5x5mm_P0.4mm,C246443
TCA9555RTWR,"U8,U9",Texas_RTW_WQFN-24-1EP_4x4mm_P0.5mm_EP2.7x2.7mm,C140277
12MHz,Y1,Crystal_SMD_3225-4Pin_3.2x2.5mm,C5310728
25MHz,Y2,Crystal_SMD_3225-4Pin_3.2x2.5mm,C9006
